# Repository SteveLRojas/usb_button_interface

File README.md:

# usb_button_interface
Interface module that maps 6 button inputs to keyboard keys.  

## What is in this repo?
Here you will find the design files for a small custom PCB that lets you connect buttons or switches to a PC via USB and map them to keyboard buttons.  
The hardware is designed in KiCad, the design files are in the HW folder.  
The firmware is written in C and meant to be compiled with Keil uVison C51 and linked with LX51. The project makes extensive use of pointers and requires a linker script for correct memory overlay.  
The entire uVision project is in the FW folder.  
The SW folder contains test scripts as well as a command line tool (ubi_programmer.py) used to set the key mapping. To set the key mapping you need ubi_programmer.py, ubi_platform.py, and ubi_regs.py. The other files are test scripts.  

## How do I use this thing?
First you will need the hardware, boards can be ordered from JLCPCB and all the components are available from LCSC.  
Once you have working hardware close the jumper J6 to put it in programming mode, compile the firmware, and use WCHISP or a similar program to upload the firmware.  
After the firmware is uploaded remove jumper J6 to put the device in functional mode. Now when it is plugged into USB the LED will blink and then stay on, this means the device is in functional mode.  
Touching the capacitive touch button will make the LED turn off, this means the device is in configuration mode. Touching the button again will put the device back into functional mode.  
Note that the capacitive button is automatically calibrated each time the device is powered on, so while powering on the device make sure it is placed in its normal operating position and don't touch the capacitive button.  
When the device is in functional mode it should appear to the PC as a completely satandard USB keyboard, when it is in configuration mode it will appear as a CDC ACM device.  
There is no need to specify a serial port when running the configuration script, as it can scan the serial ports and automatically find the device.  

## How do I set the key mapping?
Use the provided python script (ubi_programmer.py). Run it with -h to see what arguments it supports.  
Example usage: python ubi_programmer.py --eeprom --sw0 0x1A --sw1 0x29  
The above example maps sw0 to the 'W' key, and sw1 to the escape key. The hexadecimal numbers representing each keyboard key can be found in the document "HID Usage Tables for Universal Serial Bus (USB)".  
The first time you configure the device you should specify all the switches (even if you don't intend to use them) to make sure nothing is mapped to an invalid key.

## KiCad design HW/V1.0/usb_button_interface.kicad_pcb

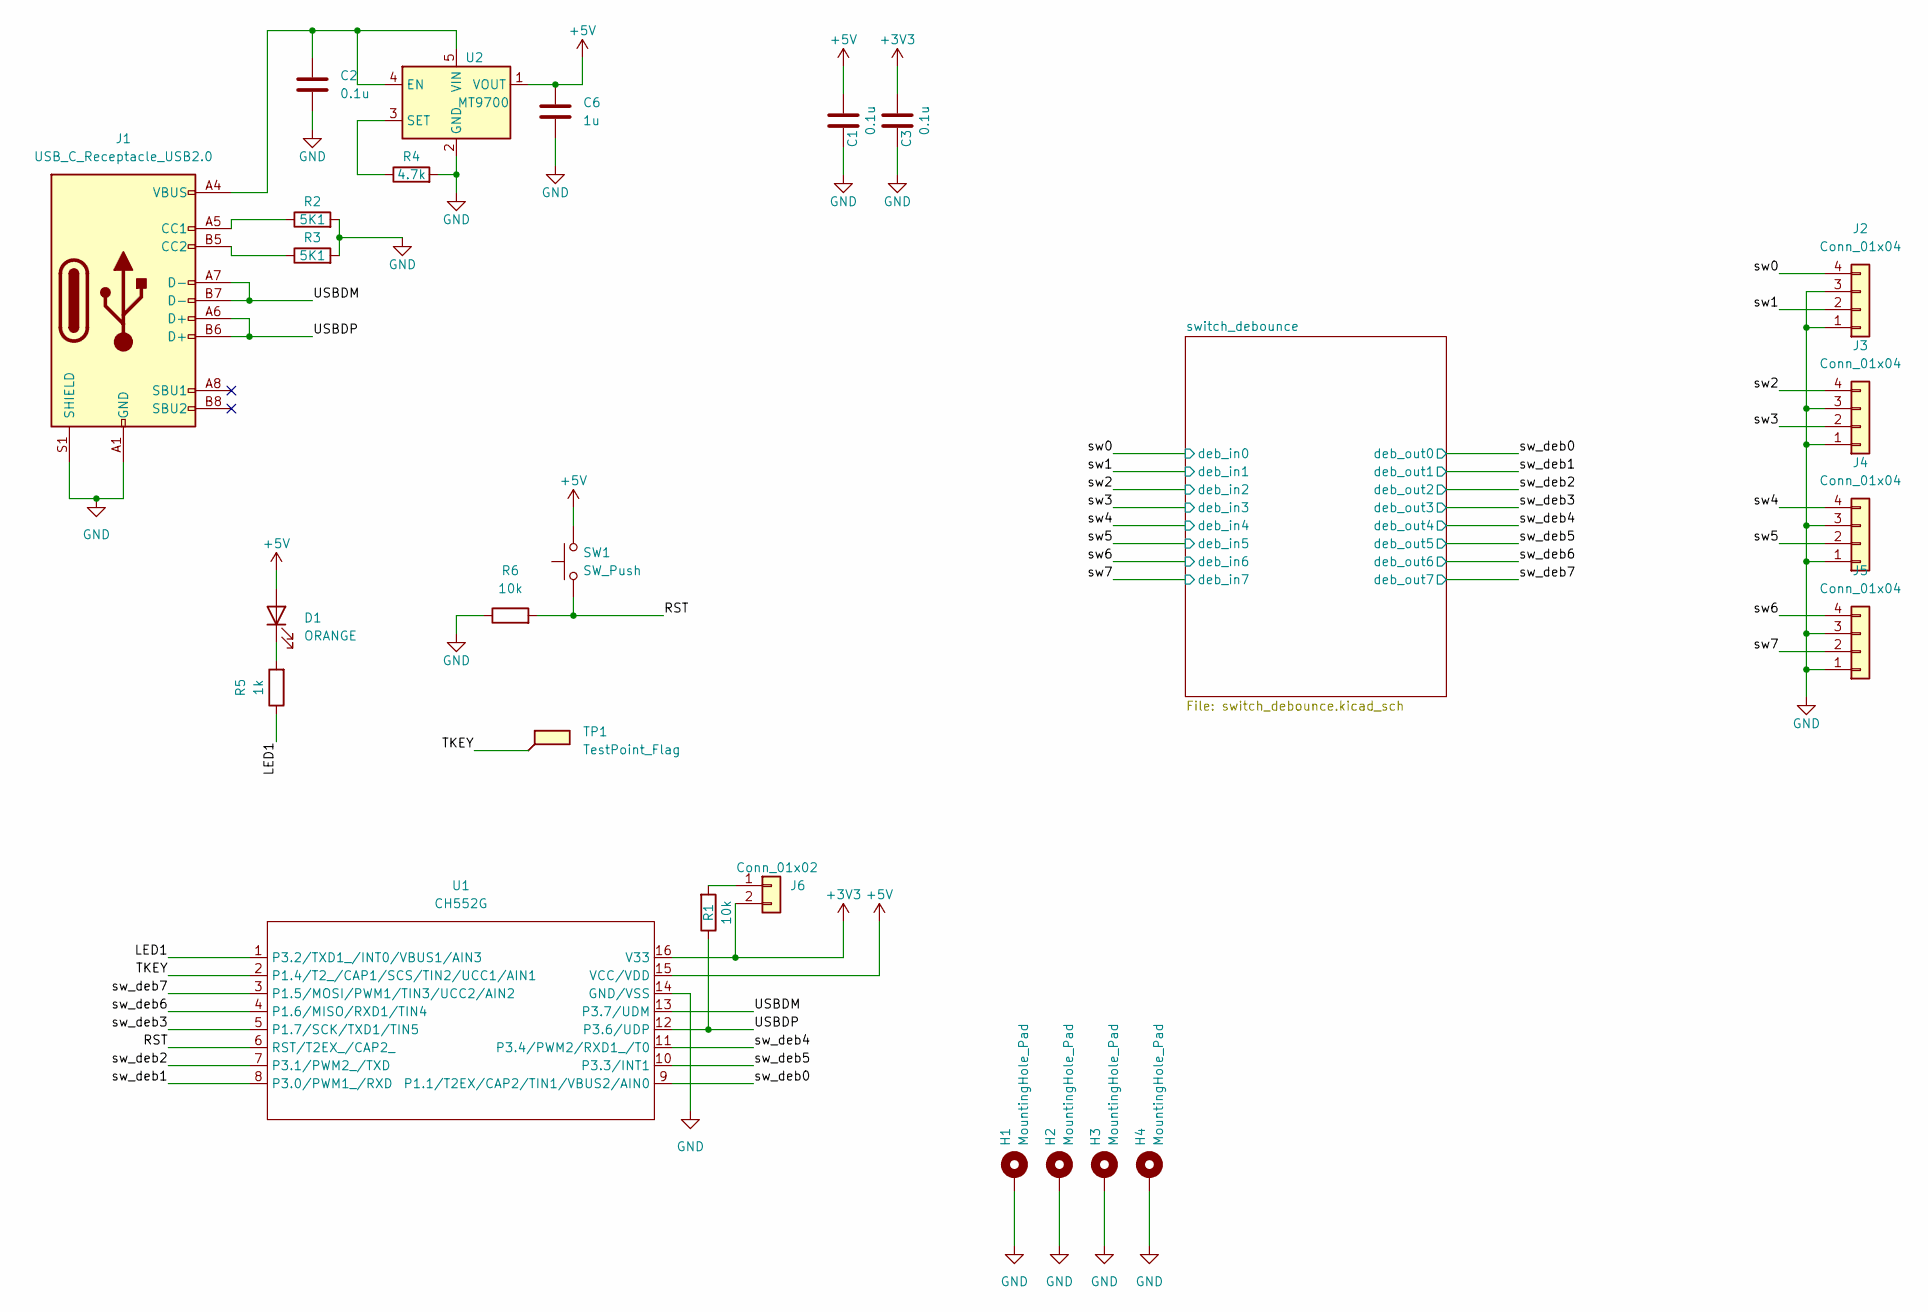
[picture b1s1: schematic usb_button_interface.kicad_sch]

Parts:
C1, C2, C3: 0.1u; C_0805_2012Metric
C6: 1u; C_0805_2012Metric
D1: ORANGE; LED_0805_2012Metric
H1, H2, H3, H4: MountingHole_Pad; MountingHole_3.2mm_M3_Pad
J1: USB_C_Receptacle_USB2.0; USB_C_Receptacle_HRO_TYPE-C-31-M-12
J2, J3, J4, J5: Conn_01x04; PhoenixContact_MC_1,5_4-G-3.81_1x04_P3.81mm_Horizontal
J6: Conn_01x02; PinHeader_1x02_P1.27mm_Vertical
R1, R6: 10k; R_0805_2012Metric
R2, R3: 5K1; R_0805_2012Metric
R4: 4.7k; R_0805_2012Metric
R5: 1k; R_0805_2012Metric
SW1: SW_Push; SW_SPST_PTS810
TP1: TestPoint_Flag; CapTouch_10mm
U1: CH552G; SO-16_3.9x9.9mm_P1.27mm
U2: MT9700; SOT-23-5

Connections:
+3V3: C3.1, J6.2, U1.16 (V33)
+5V: C1.1, C6.1, D1.2 (A), SW1.2, U1.15 (VCC/VDD), U2.1 (VOUT); also elsewhere on the board
/LED1: R5.1, U1.1 (P3.2/TXD1_/INT0/VBUS1/AIN3)
/RST: R6.2, SW1.1, U1.6 (RST/T2EX_/CAP2_)
/TKEY: TP1.1, U1.2 (P1.4/T2_/CAP1/SCS/TIN2/UCC1/AIN1)
/USBDM: J1.A7 (D-), J1.B7 (D-), U1.13 (P3.7/UDM)
/USBDP: J1.A6 (D+), J1.B6 (D+), R1.1, U1.12 (P3.6/UDP)
/sw0: J2.4; also elsewhere on the board
/sw1: J2.2; also elsewhere on the board
/sw2: J3.4; also elsewhere on the board
/sw3: J3.2; also elsewhere on the board
/sw4: J4.4; also elsewhere on the board
/sw5: J4.2; also elsewhere on the board
/sw6: J5.4; also elsewhere on the board
/sw7: J5.2; also elsewhere on the board
/sw_deb0: U1.9 (P1.1/T2EX/CAP2/TIN1/VBUS2/AIN0); also elsewhere on the board
/sw_deb1: U1.8 (P3.0/PWM1_/RXD); also elsewhere on the board
/sw_deb2: U1.7 (P3.1/PWM2_/TXD); also elsewhere on the board
/sw_deb3: U1.5 (P1.7/SCK/TXD1/TIN5); also elsewhere on the board
/sw_deb4: U1.11 (P3.4/PWM2/RXD1_/T0); also elsewhere on the board
/sw_deb5: U1.10 (P3.3/INT1); also elsewhere on the board
/sw_deb6: U1.4 (P1.6/MISO/RXD1/TIN4); also elsewhere on the board
/sw_deb7: U1.3 (P1.5/MOSI/PWM1/TIN3/UCC2/AIN2); also elsewhere on the board
GND: C1.2, C2.2, C3.2, C6.2, H1.1, H2.1, H3.1, H4.1, J1.A1 (GND), J1.A12 (GND), J1.B1 (GND), J1.B12 (GND), J1.S1 (SHIELD), J2.1, J2.3, J3.1, J3.3, J4.1, J4.3, J5.1, J5.3, R2.2, R3.2, R4.2, R6.1, U1.14 (GND/VSS), U2.2 (GND); also elsewhere on the board
unnamed: C2.1, J1.A4 (VBUS), J1.A9 (VBUS), J1.B4 (VBUS), J1.B9 (VBUS), U2.4 (EN), U2.5 (VIN)
unnamed: D1.1 (K), R5.2
unnamed: J1.A5 (CC1), R2.1
unnamed: J1.B5 (CC2), R3.1
unnamed: J6.1, R1.2
unnamed: R4.1, U2.3 (SET)

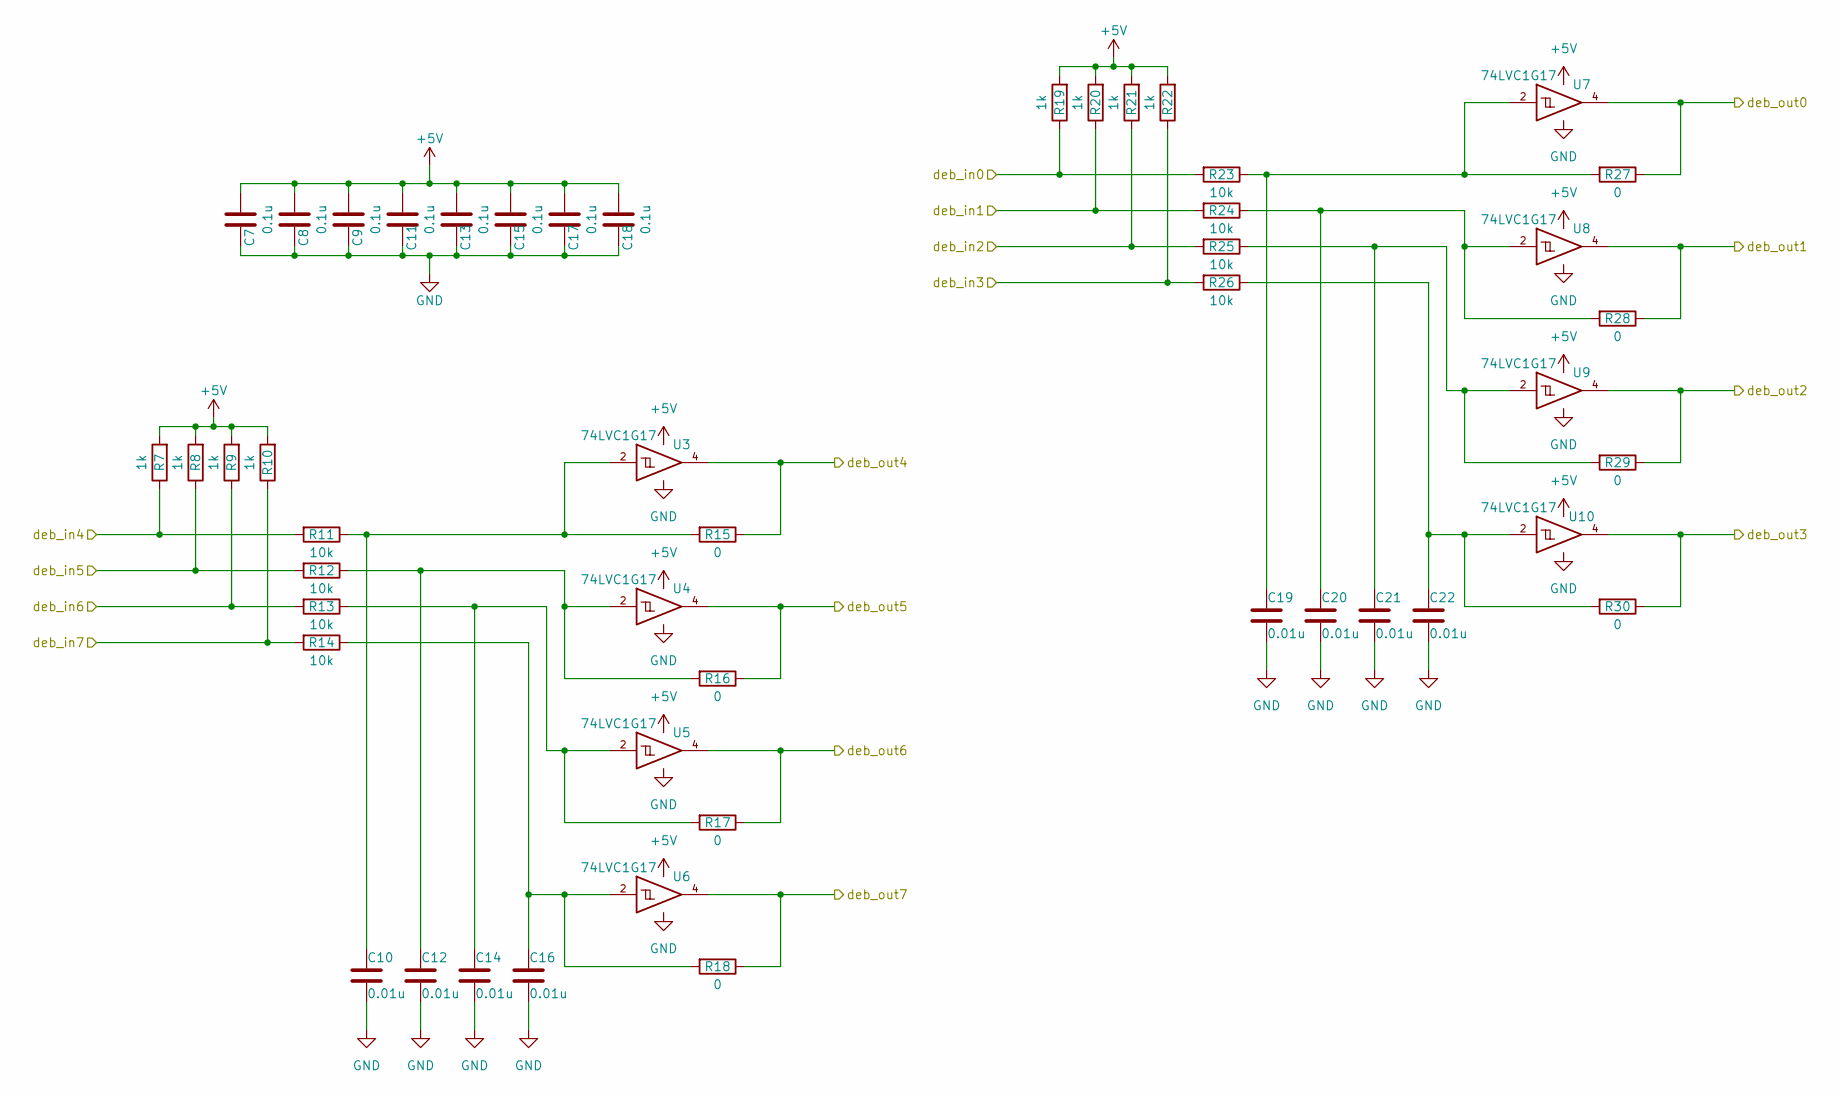
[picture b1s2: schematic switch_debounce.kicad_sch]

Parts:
C7, C8, C9, C11, C13, C15, C17, C18: 0.1u; C_0805_2012Metric
C10, C12, C14, C16, C19, C20, C21, C22: 0.01u; C_0805_2012Metric
R7, R8, R9, R10, R19, R20, R21, R22: 1k; R_0805_2012Metric
R11, R12, R13, R14, R23, R24, R25, R26: 10k; R_0805_2012Metric
R15, R16, R17, R18, R27, R28, R29, R30: 0; R_0805_2012Metric
U3, U4, U5, U6, U7, U8, U9, U10: 74LVC1G17; SOT-353_SC-70-5

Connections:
+5V: C7.1, C8.1, C9.1, C11.1, C13.1, C15.1, C17.1, C18.1, R7.2, R8.2, R9.2, R10.2, R19.2, R20.2, R21.2, R22.2, U3.5 (VCC), U4.5 (VCC), U5.5 (VCC), U6.5 (VCC), U7.5 (VCC), U8.5 (VCC), U9.5 (VCC), U10.5 (VCC); also elsewhere on the board
/sw0: R19.1, R23.2; also elsewhere on the board
/sw1: R20.1, R24.2; also elsewhere on the board
/sw2: R21.1, R25.2; also elsewhere on the board
/sw3: R22.1, R26.2; also elsewhere on the board
/sw4: R7.1, R11.2; also elsewhere on the board
/sw5: R8.1, R12.2; also elsewhere on the board
/sw6: R9.1, R13.2; also elsewhere on the board
/sw7: R10.1, R14.2; also elsewhere on the board
/sw_deb0: R27.1, U7.4; also elsewhere on the board
/sw_deb1: R28.1, U8.4; also elsewhere on the board
/sw_deb2: R29.1, U9.4; also elsewhere on the board
/sw_deb3: R30.1, U10.4; also elsewhere on the board
/sw_deb4: R15.1, U3.4; also elsewhere on the board
/sw_deb5: R16.1, U4.4; also elsewhere on the board
/sw_deb6: R17.1, U5.4; also elsewhere on the board
/sw_deb7: R18.1, U6.4; also elsewhere on the board
GND: C7.2, C8.2, C9.2, C10.1, C11.2, C12.1, C13.2, C14.1, C15.2, C16.1, C17.2, C18.2, C19.1, C20.1, C21.1, C22.1, U3.3 (GND), U4.3 (GND), U5.3 (GND), U6.3 (GND), U7.3 (GND), U8.3 (GND), U9.3 (GND), U10.3 (GND); also elsewhere on the board
unnamed: C10.2, R11.1, R15.2, U3.2
unnamed: C12.2, R12.1, R16.2, U4.2
unnamed: C14.2, R13.1, R17.2, U5.2
unnamed: C16.2, R14.1, R18.2, U6.2
unnamed: C19.2, R23.1, R27.2, U7.2
unnamed: C20.2, R24.1, R28.2, U8.2
unnamed: C21.2, R25.1, R29.2, U9.2
unnamed: C22.2, R26.1, R30.2, U10.2

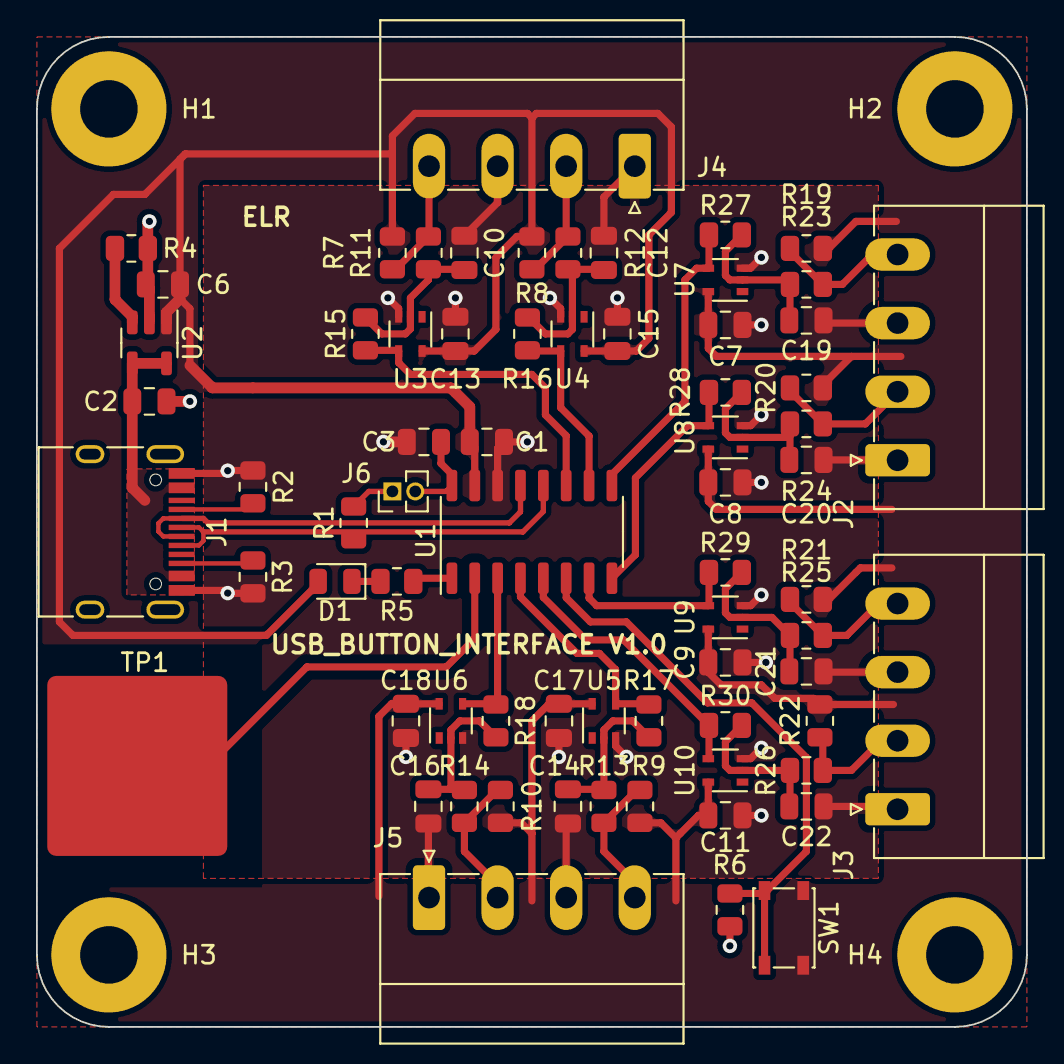
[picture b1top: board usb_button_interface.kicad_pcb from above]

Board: 2 copper layers, 55.0 x 55.0 mm, 73 parts (0 on the bottom side), 38 nets.
